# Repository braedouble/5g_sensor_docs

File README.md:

# Hardware
- My sensor (Diagram)
	- 
- My sensor (On shaker)
	- 
## 5G Connection
- Sensor connects to 5G via ethernet CPE access point
- Connects to a device connected directly to the 5G core server
	- This port is connected to an ethernet port in the lab, the local breakout port (LBO)

## MCU
- WT32 - all important info below
	- https://github.com/egnor/wt32-eth01 (Guide)
		- most helpful for setup, tricks for WT32
		- HOW TO PROGRAM -> program mode vs run mode (IO0)
	- https://en.wireless-tag.com/product-item-2.html (INFO)

## Accelerometer
All read via SPI (analog sensor add ADC)
- ICM42688-P
	- Custom PCB (datasheet pg. 21 typical operating circuit)
		- Included in files
		- Easy for me to order more, just contact me
	- https://invensense.tdk.com/products/motion-tracking/6-axis/icm-42688-p/ (INFO)
	- https://invensense.tdk.com/wp-content/uploads/2020/04/ds-000347_icm-42688-p-datasheet.pdf (DATASHEET)
# Software
## Libraries
All info based on register functions from accelerometer datasheets
- ICM42688-P
	- mainly based on https://github.com/finani/ICM42688
	- some changes to try to make SPI reads faster and match some functions to my other accelerometer libraries
	- did some work to get FIFO working to try for 32 kHz output
	- tested and working with 5G and ethernet at 16kHz ODR with interrupt method
## Platformio/ESP32
- Used for code uploading 
	- https://randomnerdtutorials.com/vs-code-platformio-ide-esp32-esp8266-arduino/
		- GOOD GUIDE - platformio for esp32 install and setup
	- https://platformio.org/install
	- https://docs.platformio.org/en/latest/boards/espressif32/wt32-eth01.html?utm_source=platformio&utm_medium=piohome
		- WT32 board setup (select for board in platformio)
## Receiver
- Require python and matplotlib library (rest of libraries should be built in)
# Setup
- Follow platformio setup
- Setup WT32 for programming per the guide
- Code should be okay to upload to sensor
	- sensor
		- set IP address and port number of receiver 
	- receiver
		- match port number to sensor
- Change to run mode and connect to a python reader
## FOR SENSOR
- Needs valid network info (reader IP address and port)
- Sensor settings for Hz and range are set via code still I think for ICM, controls need to be finished
- 16kHz max ODR for SPI without FIFO right now
## FOR RECEIVER
- Needs port set for same as reader 
- Needs sensor on and running first
# Lathe Tool Holder Previous Works
- Bleicher 2018, 2020, 2023 (Milling)
  	- Schorghofer 2019
	- Ramsauer 2021 (not much sensor info added here)
## Main Changes
- Mounting (tool holder)
	- machine considerations (chips, coolant, heat)
	- cpe placement / battery life
- Read selected sensors
- Rec./Controller updates + database implementation
- Sensor connection / reconnection handling

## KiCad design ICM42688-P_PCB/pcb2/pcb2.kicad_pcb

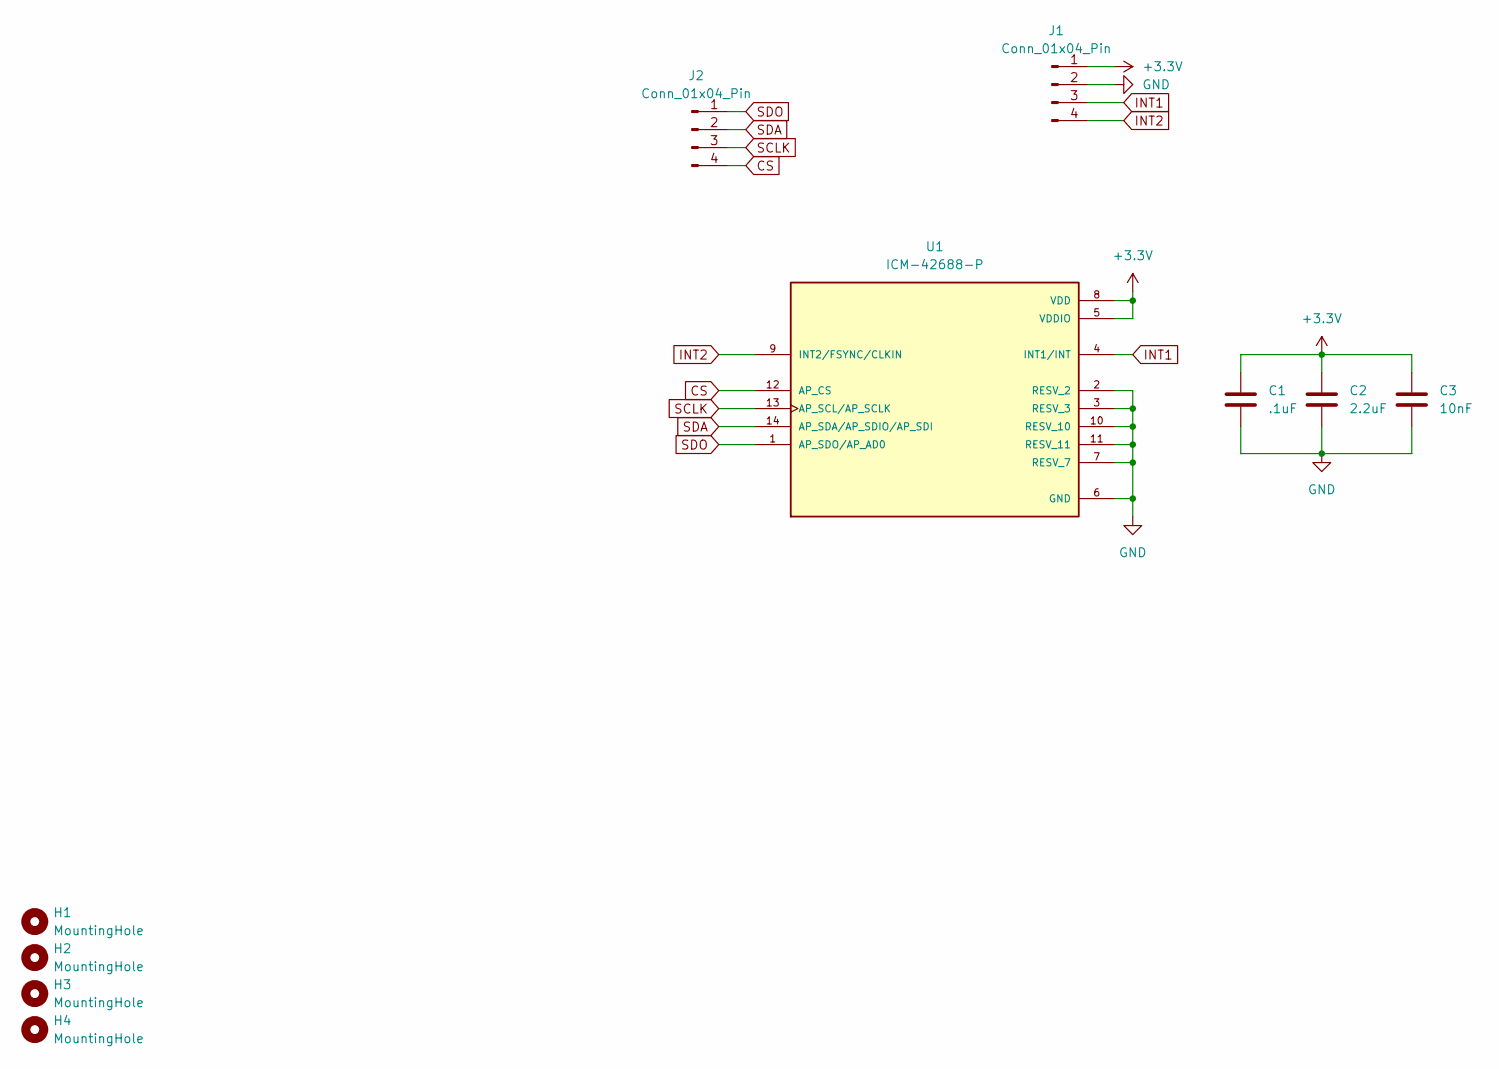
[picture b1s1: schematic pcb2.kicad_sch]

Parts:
C1: .1uF; C_0402_1005Metric; JLCPCB Part # C1525
C2: 2.2uF; C_0402_1005Metric; JLCPCB Part # C12530
C3: 10nF; C_0402_1005Metric; JLCPCB Part # C15195
H1, H2, H3, H4: MountingHole; MountingHole_3mm
J1, J2: Conn_01x04_Pin; PinHeader_1x04_P2.54mm_Vertical
U1: ICM-42688-P; PQFN50P300X250X97-14N; PARTREV 1.2; JLCPCB Part # C1850418

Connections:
+3.3V: C1.1, C2.1, C3.1, J1.1, U1.5 (VDDIO), U1.8 (VDD)
CS: J2.4, U1.12 (AP_CS)
GND: C1.2, C2.2, C3.2, J1.2, U1.2 (RESV_2), U1.3 (RESV_3), U1.6 (GND), U1.7 (RESV_7), U1.10 (RESV_10), U1.11 (RESV_11)
INT1: J1.3, U1.4 (INT1/INT)
INT2: J1.4, U1.9 (INT2/FSYNC/CLKIN)
SCLK: J2.3, U1.13 (AP_SCL/AP_SCLK)
SDA: J2.2, U1.14 (AP_SDA/AP_SDIO/AP_SDI)
SDO: J2.1, U1.1 (AP_SDO/AP_AD0)

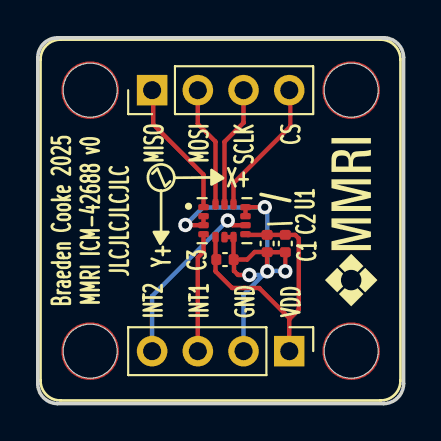
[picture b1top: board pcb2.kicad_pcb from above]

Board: 2 copper layers, 20.3 x 20.3 mm, 10 parts (0 on the bottom side), 8 nets.

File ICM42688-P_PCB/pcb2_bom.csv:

"Reference","Value","Footprint","JLCPCB Part #","Package","Qty"
"C1",".1uF","Capacitor_SMD:C_0402_1005Metric","C1525","0402","1"
"C2","2.2uF","Capacitor_SMD:C_0402_1005Metric","C12530","0402","1"
"C3","10nF","Capacitor_SMD:C_0402_1005Metric","C15195","0402","1"
"H1-H4","MountingHole","MountingHole:MountingHole_3mm","","","4"
"J1, J2","Conn_01x04_Pin","Connector_PinHeader_2.54mm:PinHeader_1x04_P2.54mm_Vertical","","","2"
"U1","ICM-42688-P","ICM-42688-P:PQFN50P300X250X97-14N","C1850418","LGA-14 TDK InvenSense","1"

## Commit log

2025-09-23 icm ethernet stuff from laptop
    ICM ethernet sensor info
    - pcb info
    - general info
    - programming setup
    - code plus important parameters
    - sensor and rec code
2025-10-03 add 5g connection info
